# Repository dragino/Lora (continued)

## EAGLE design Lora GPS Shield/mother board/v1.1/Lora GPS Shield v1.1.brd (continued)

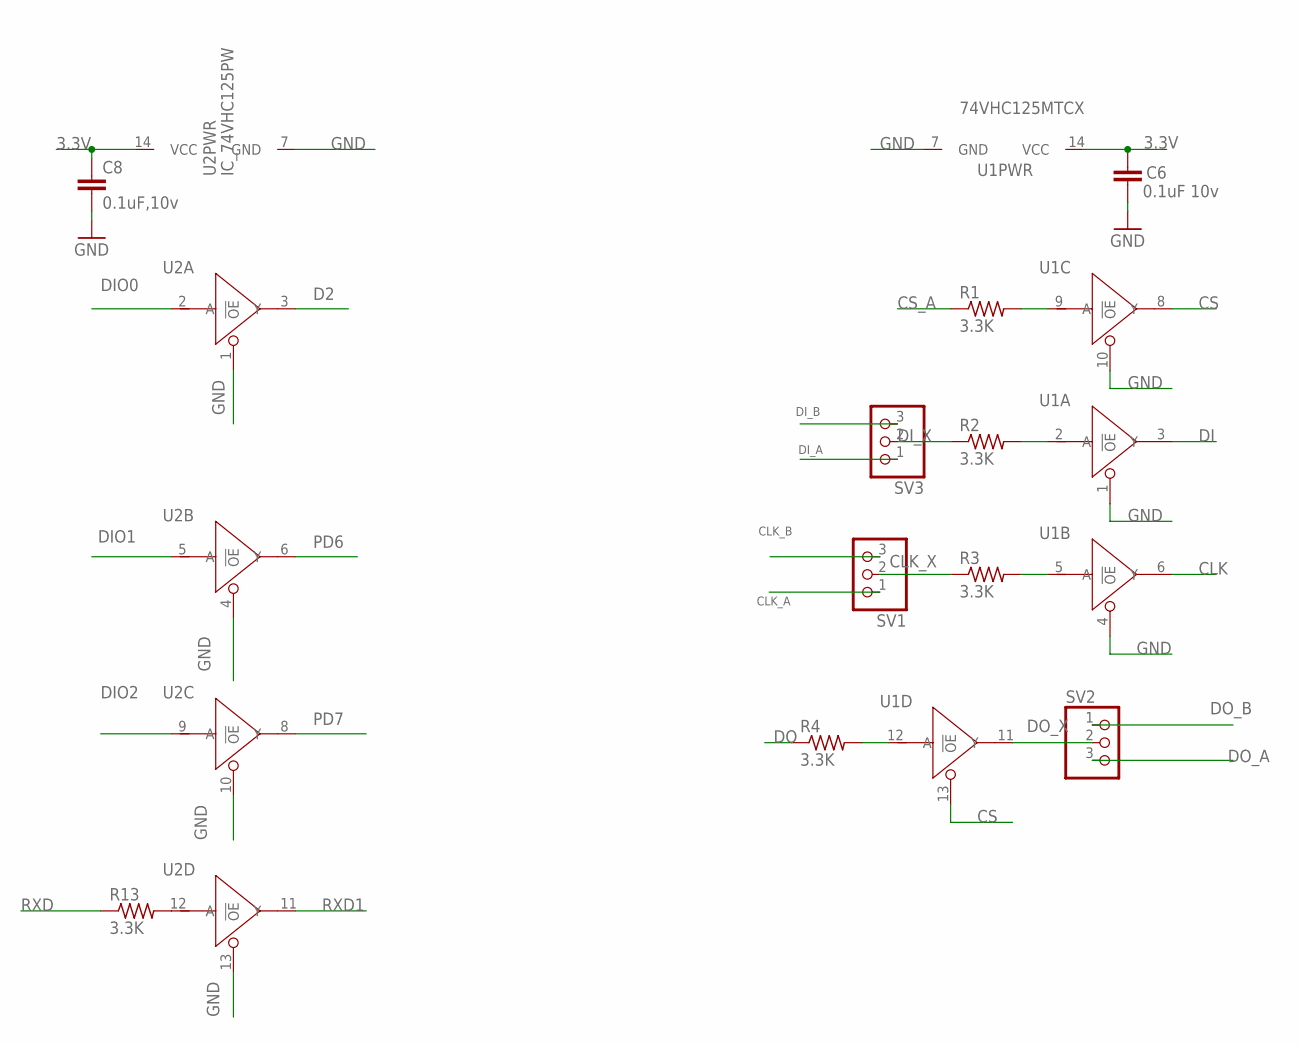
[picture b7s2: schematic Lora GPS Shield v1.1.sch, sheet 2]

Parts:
C6: 0.1uF 10v; C0402
C8: 0.1uF,10v; C0402
R1, R2, R3, R4, R13: 3.3K; R0402
SV1: PINHD-1X31X3_S; 1X03
SV2, SV3: PINHD-1X3; 1X03
U1: 74VHC125MTCX; TSSOP14
U2: IC_74VHC125PW; IC_TSSOP14

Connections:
3.3V: C6.2, C8.1, U1.14 (VCC), U2.14 (VCC); also elsewhere on the board
CLK: U1.6 (Y); also elsewhere on the board
CLK_A: SV1.1; also elsewhere on the board
CLK_B: SV1.3; also elsewhere on the board
CLK_X: R3.1, SV1.2
CS: U1.8 (Y), U1.13 (!OE); also elsewhere on the board
CS_A: R1.1; also elsewhere on the board
D2: U2.3 (Y); also elsewhere on the board
DI: U1.3 (Y); also elsewhere on the board
DIO0: U2.2 (A); also elsewhere on the board
DIO1: U2.5 (A); also elsewhere on the board
DIO2: U2.9 (A); also elsewhere on the board
DI_A: SV3.1; also elsewhere on the board
DI_B: SV3.3; also elsewhere on the board
DI_X: R2.1, SV3.2
DO: R4.1; also elsewhere on the board
DO_A: SV2.3; also elsewhere on the board
DO_B: SV2.1; also elsewhere on the board
DO_X: SV2.2, U1.11 (Y)
GND: C6.1, C8.2, U1.1 (!OE), U1.4 (!OE), U1.7 (GND), U1.10 (!OE), U2.1 (!OE), U2.4 (!OE), U2.7 (GND), U2.10 (!OE), U2.13 (!OE); also elsewhere on the board
unnamed: R4.2, U1.12 (A)
unnamed: R3.2, U1.5 (A)
unnamed: R2.2, U1.2 (A)
unnamed: R1.2, U1.9 (A)
unnamed: R13.2, U2.12 (A)
PD6: U2.6 (Y); also elsewhere on the board
PD7: U2.8 (Y); also elsewhere on the board
RXD: R13.1; also elsewhere on the board
RXD1: U2.11 (Y); also elsewhere on the board

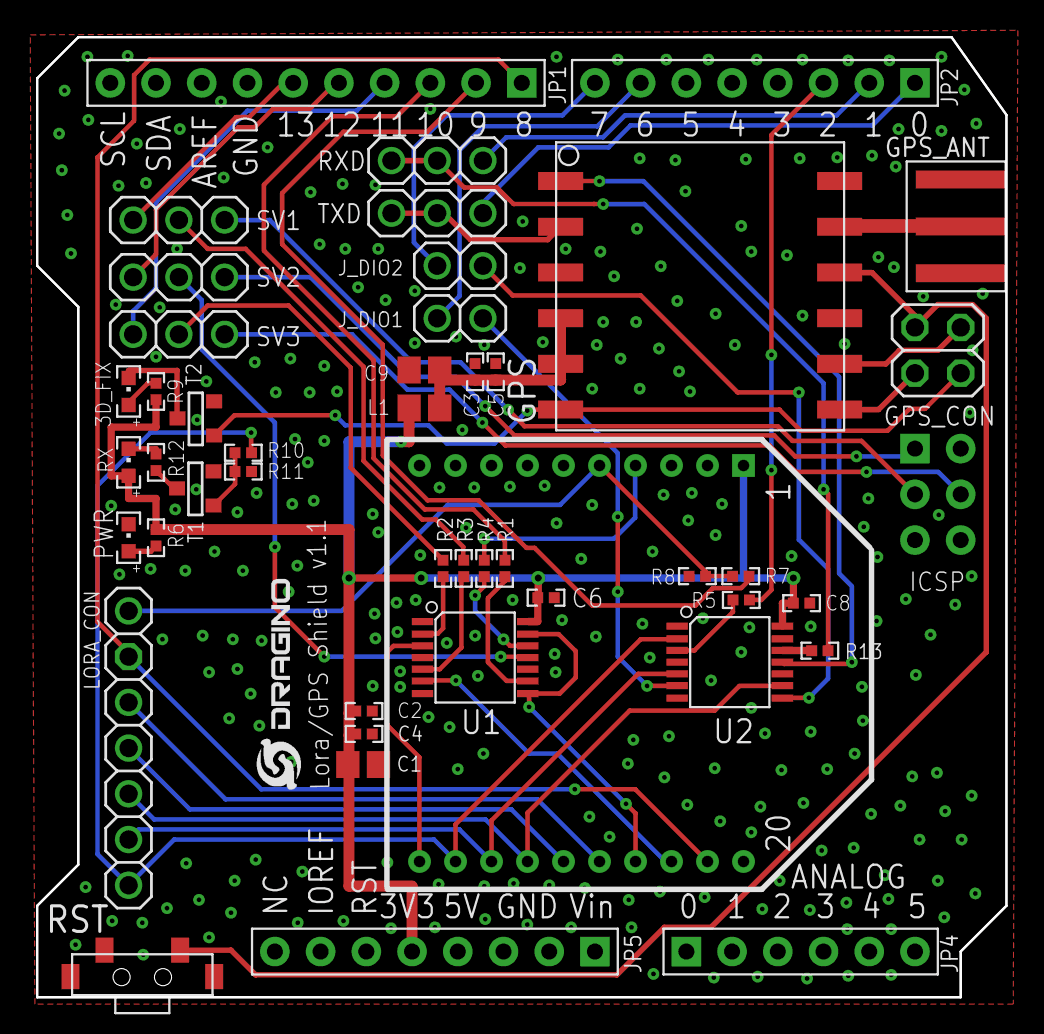
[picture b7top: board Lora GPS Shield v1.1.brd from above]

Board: 2 copper layers, 53.8 x 53.3 mm, 44 parts (0 on the bottom side), 52 nets.

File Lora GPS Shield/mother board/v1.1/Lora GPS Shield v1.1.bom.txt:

Partlist exported from D:/Projects/Lora Serial/Lora GPS Shield/v1.1/Lora GPS Shield v1.1.sch at 2016/7/25 9:24

Part     Value                Device                                 Package              Description                     MF MPN OC_FARNELL OC_NEWARK
3D_FIX   Green                LEDCHIPLED_0603                        CHIPLED_0603         LED                                                        
C1       10uF 10v             C-EUC0805                              C0805                CAPACITOR, European symbol                                 
C2       NL                   C-EUC0402                              C0402                CAPACITOR, European symbol                                 
C3       0.1uF 10v            C-EUC0402                              C0402                CAPACITOR, European symbol                                 
C4       1uF 10v              C-EUC0402                              C0402                CAPACITOR, European symbol                                 
C5       0.1uF 10v            C-EUC0402                              C0402                CAPACITOR, European symbol                                 
C6       0.1uF 10v            C-EUC0402                              C0402                CAPACITOR, European symbol                                 
C8       0.1uF,10v            C-EUC0402                              C0402                CAPACITOR, European symbol                                 
C9       10uF                 C-EUC0805                              C0805                CAPACITOR, European symbol                                 
GPS      L80                  L80                                    L80                                                                             
GPS_ANT  NL                   SMA-KE                                 SMA-KE                                                                          
GPS_CON                       PINHD-2X2                              2X02                 PIN HEADER                                                 
J_DIO1                        PINHD-1X21X2_S                         1X02                 PIN HEADER                                                 
J_DIO2                        PINHD-1X2                              1X02                 PIN HEADER                                                 
L1       JLC-PZ2012D800-3R0TF BEADS0805                              C0805                                                                           
LORA_CON                      PINHD-1X71X7_S                         1X07                 PIN HEADER                                                 
PWR      Green                DRAGINO_LEDCHIPLED_0603                DRAGINO_CHIPLED_0603 LED                                                        
R1       3.3K                 R-US_R0402                             R0402                RESISTOR, American symbol                                  
R2       3.3K                 R-US_R0402                             R0402                RESISTOR, American symbol                                  
R3       3.3K                 R-US_R0402                             R0402                RESISTOR, American symbol                                  
R4       3.3K                 R-US_R0402                             R0402                RESISTOR, American symbol                                  
R5       0                    R-US_R0402                             R0402                RESISTOR, American symbol                                  
R6       330R                 R-US_R0402                             R0402                RESISTOR, American symbol                                  
R7       1K                   R-US_R0402                             R0402                RESISTOR, American symbol                                  
R8       NL                   R-US_R0402                             R0402                RESISTOR, American symbol                                  
R9       330R                 R-US_R0402                             R0402                RESISTOR, American symbol                                  
R10      47k                  R-US_R0402                             R0402                RESISTOR, American symbol                                  
R11      47k                  R-US_R0402                             R0402                RESISTOR, American symbol                                  
R12      510pR                R-US_R0402                             R0402                RESISTOR, American symbol                                  
R13      3.3K                 R-US_R0402                             R0402                RESISTOR, American symbol                                  
RST      SWITCHTS-017         SWITCHTS-017                           TS-017                                                                          
RX       BLUE                 LEDCHIPLED_0603                        CHIPLED_0603         LED                                                        
RXD                           PINHD-1X3                              1X03                 PIN HEADER                                                 
SV1                           PINHD-1X31X3_S                         1X03                 PIN HEADER                                                 
SV2                           PINHD-1X3                              1X03                 PIN HEADER                                                 
SV3                           PINHD-1X3                              1X03                 PIN HEADER                                                 
T1       BSS138/SOT23         NMOSFET-SOT23                          SOT-23               MOS FET                                unknown    unknown  
T2       BSS138/SOT23         NMOSFET-SOT23                          SOT-23               MOS FET                                unknown    unknown  
TXD                           PINHD-1X3                              1X03                 PIN HEADER                                                 
U$1      LOGO-NEW             LOGO-NEW                               LOGO-SILK-NEW                                                                   
U1       74VHC125MTCX         74VHC125PW                             TSSOP14              Quad Buffer/Line Driver;3-state                            
U2       IC_74VHC125PW        IC_74VHC125PW                          IC_TSSOP14           Quad Buffer/Line Driver;3-state                            
U3       BEE                  LORAHAT_S                              LORA                                                                            
U5                            MOUDLE_ARDUINO-38PMOUDLE_ARDUINO-38P_L MOUDLE_ARDUINO-38P_L
